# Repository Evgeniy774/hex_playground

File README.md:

# hex_playground
Simple STM32F411 based project for kids education purposes

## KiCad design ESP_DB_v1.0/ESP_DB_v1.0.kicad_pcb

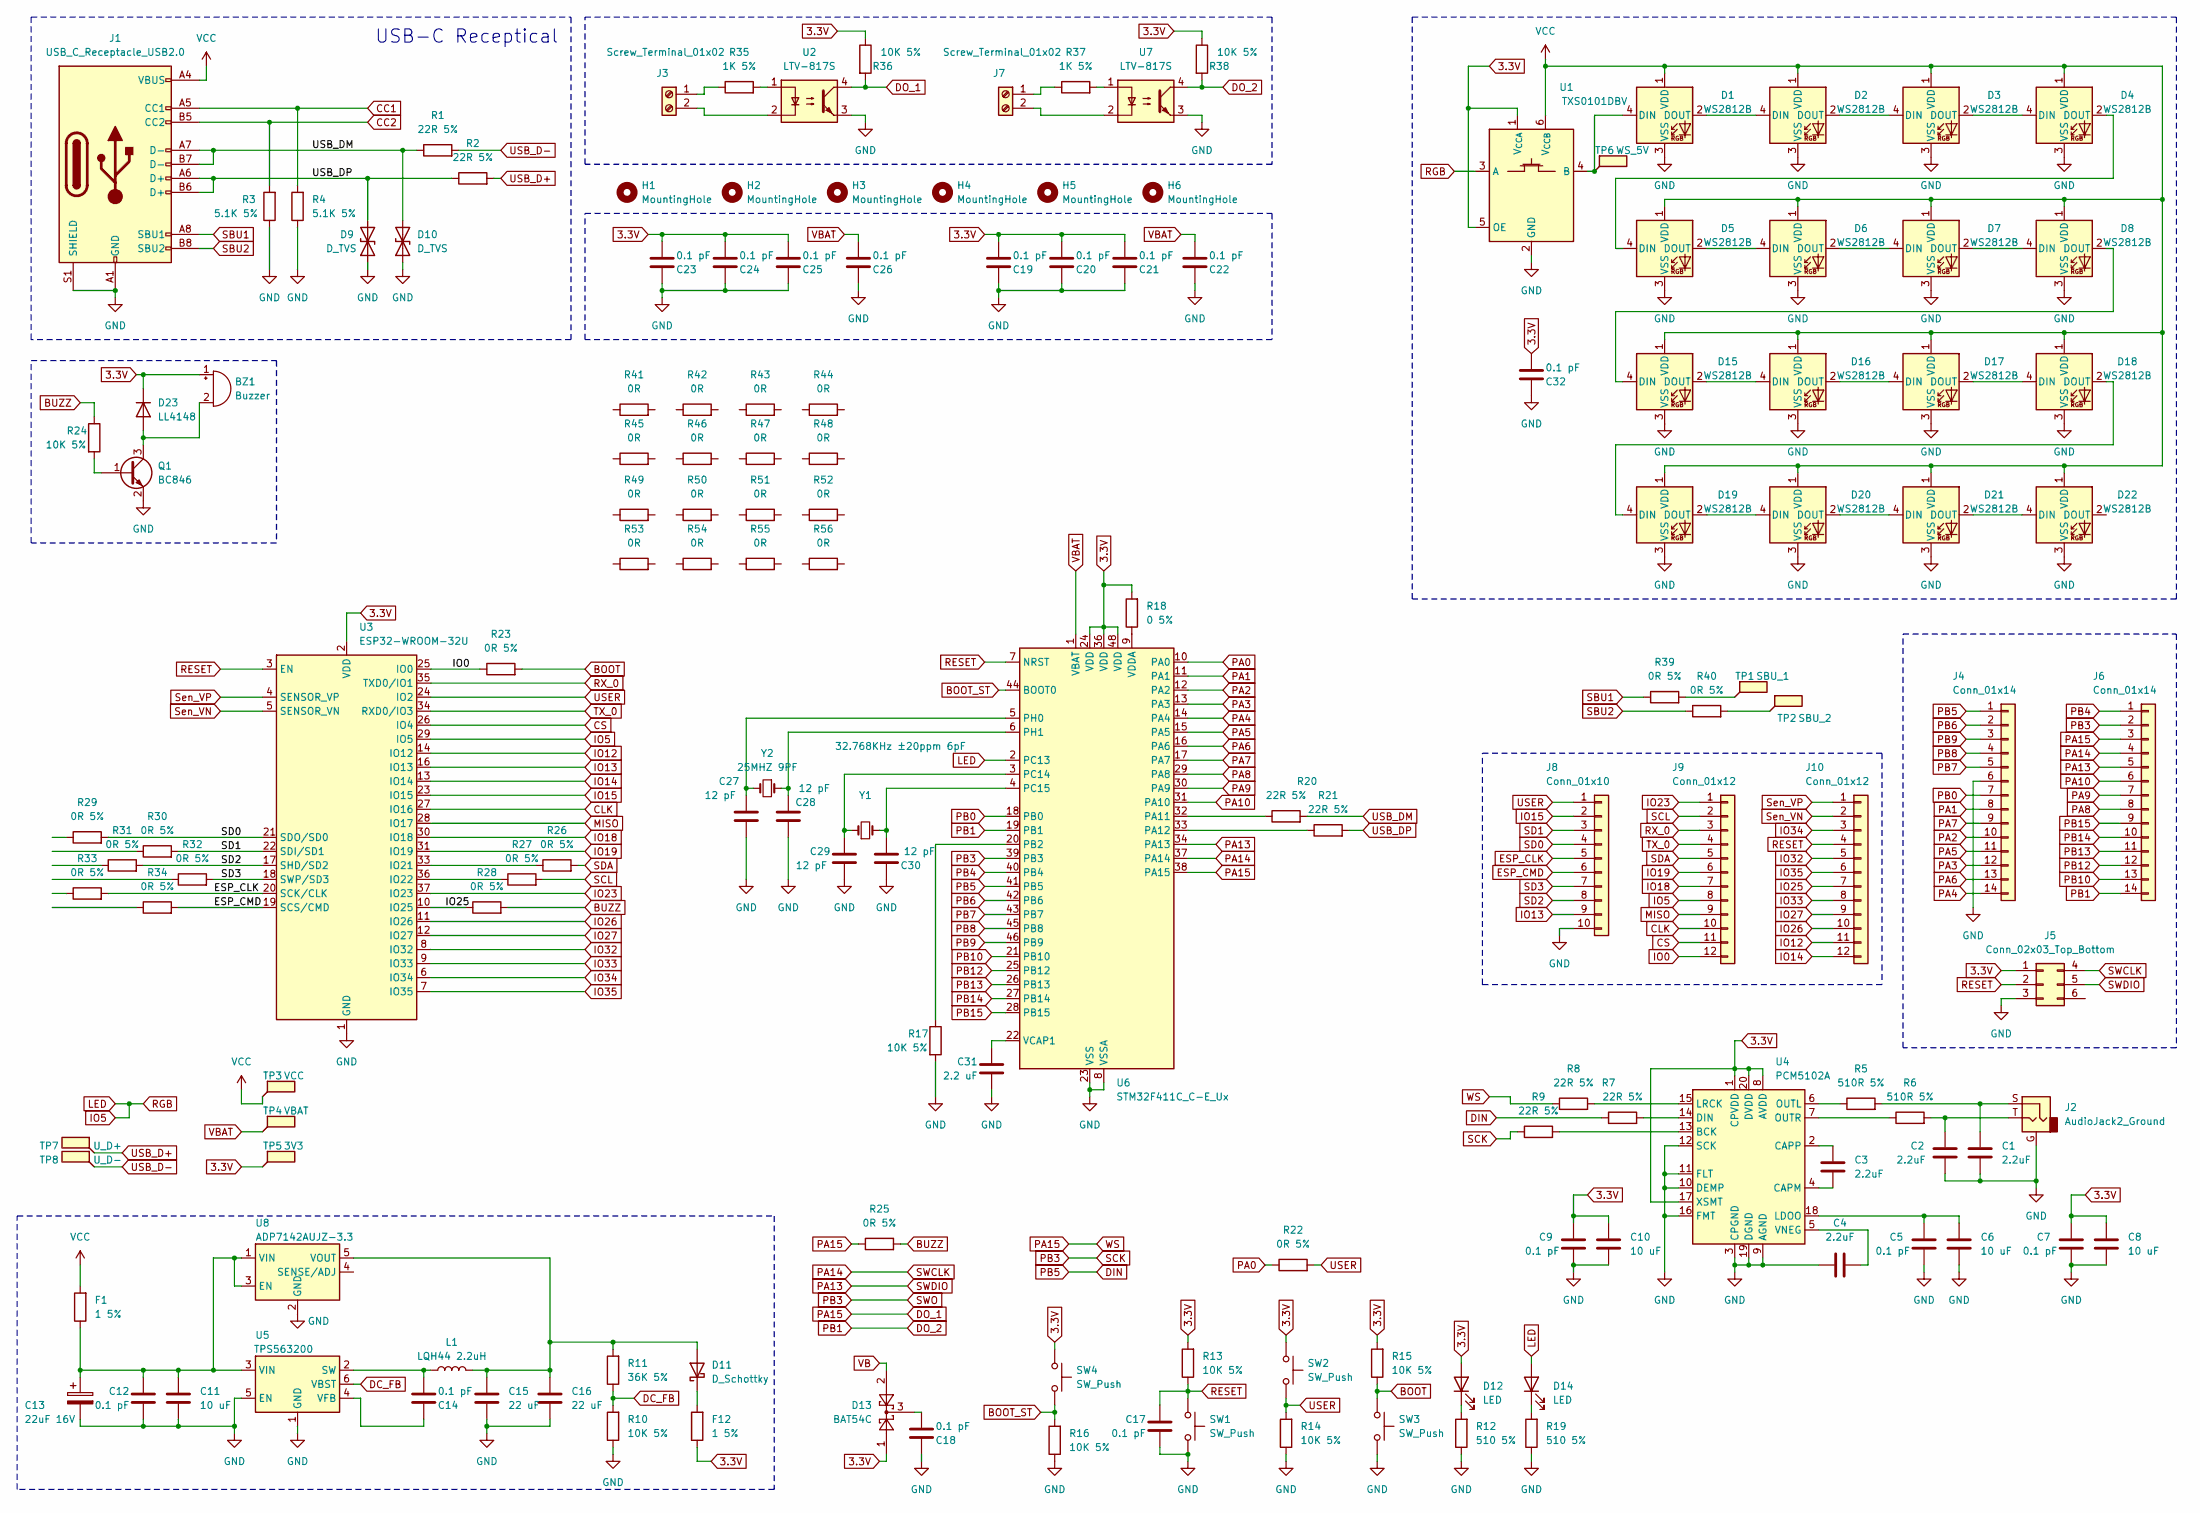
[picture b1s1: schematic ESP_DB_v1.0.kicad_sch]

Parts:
BZ1: Buzzer; Buzzer_D14mm_H7mm_P10mm
C1, C2, C3, C4: 2.2uF; C_0603_1608Metric_EK
C5, C7, C9, C12, C14, C17, C18, C19, C20, C21, C22, C23, C24, C25, C26, C32: 0.1 pF; C_0603_1608Metric_EK
C6, C8, C10, C11: 10 uF; C_0603_1608Metric_EK
C13: 22uF 16V; CP_EIA-3528-21_Kemet-B
C15, C16: 22 uF; C_0603_1608Metric_EK
C27, C28, C29, C30: 12 pF; C_0603_1608Metric_EK
C31: 2.2 uF; C_0603_1608Metric_EK
D1, D2, D3, D4, D5, D6, D7, D8, D15, D16, D17, D18, D19, D20, D21, D22: WS2812B; LED_WS2812B_PLCC4_5.0x5.0mm_P3.2mm
D9, D10: D_TVS; D_0805_2012Metric
D11: D_Schottky; D_SOD-123
D12, D14: LED; LED_0603_1608Metric
D13: BAT54C; SOT-23
D23: LL4148; D_MiniMELF
F1, F12: 1 5%; C_1206_3216Metric
H1, H2, H3, H4, H5, H6: MountingHole; MountingHole_3.2mm_M3_Pad_Via
J1: USB_C_Receptacle_USB2.0; USB_C_Receptacle_16_JAE_GT-USB-7010ASV
J2: AudioJack2_Ground; Jack_3.5mm_CUI_SJ1-3533NG_Horizontal
J3, J7: Screw_Terminal_01x02; PhoenixContact_MCV_1,5_2-G-3.81_1x02_P3.81mm_Vertical
J4, J6: Conn_01x14; PinHeader_2x07_P2.54mm_Vertical
J5: Conn_02x03_Top_Bottom; PinHeader_2x03_P2.00mm_Vertical
J8: Conn_01x10; PinHeader_1x10_P2.54mm_Vertical
J9, J10: Conn_01x12; PinHeader_2x06_P2.54mm_Vertical
L1: LQH44 2.2uH; L_Wurth_WE-LQSH-4020
Q1: BC846; SOT-23_EK
R1, R2, R7, R8, R9, R20, R21: 22R 5%; R_0603_1608Metric_EK
R3, R4: 5.1K 5%; R_0603_1608Metric_EK
R5, R6: 510R 5%; R_0603_1608Metric_EK
R10, R13, R14, R15, R16, R17, R24, R36, R38: 10K 5%; R_0603_1608Metric_EK
R11: 36K 5%; R_0603_1608Metric_EK
R12, R19: 510 5%; R_0603_1608Metric_EK
R18: 0 5%; R_0603_1608Metric_EK
R22, R23, R25, R26, R27, R28, R29, R30, R31, R32, R33, R34, R39, R40: 0R 5%; R_0603_1608Metric_EK
R35, R37: 1K 5%; R_0603_1608Metric_EK
R41, R42, R43, R44, R45, R46, R47, R48, R49, R50, R51, R52, R53, R54, R55, R56: 0R; R_0603_1608Metric_EK
SW1, SW2, SW3, SW4: SW_Push; SW_Push_1P1T_XKB_TS-1187A
TP1: SBU_1; TestPoint_Loop_D2.60mm_Drill0.9mm_Beaded
TP2: SBU_2; TestPoint_Loop_D2.60mm_Drill0.9mm_Beaded
TP3: VCC; TestPoint_Loop_D2.60mm_Drill0.9mm_Beaded
TP4: VBAT; TestPoint_Loop_D2.60mm_Drill0.9mm_Beaded
TP5: 3V3; TestPoint_Loop_D2.60mm_Drill0.9mm_Beaded
TP6: WS_5V; TestPoint_Loop_D2.60mm_Drill0.9mm_Beaded
TP7: U_D+; TestPoint_Keystone_5000-5004_Miniature
TP8: U_D-; TestPoint_Keystone_5000-5004_Miniature
U1: TXS0101DBV; SOT-23-6
U2, U7: LTV-817S; SMDIP-4_W9.53mm
U3: ESP32-WROOM-32U
U4: PCM5102A; TSSOP-20_4.4x6.5mm_P0.65mm
U5: TPS563200; SOT-23-6
U6: STM32F411C_C-E_Ux; QFN-48-1EP_7x7mm_P0.5mm_EP5.6x5.6mm
U8: ADP7142AUJZ-3.3; TSOT-23-5
Y1: 32.768KHz ±20ppm 6pF; Crystal_SMD_3215-2Pin_3.2x1.5mm
Y2: 25MHZ 9PF; Crystal_SMD_3225-4Pin_3.2x2.5mm

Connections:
3.3V: BZ1.1 (-), C7.1, C8.1, C9.1, C10.1, C19.2, C20.2, C21.2, C23.2, C24.2, C25.2, C32.2, D12.2 (A), D13.1, D23.1 (K), F12.1, J5.1, R13.2, R15.2, R18.2, R36.1, R38.1, SW2.1, SW4.1, TP5.1, U1.1 (V_{CCA}), U1.5 (OE), U3.2 (VDD), U4.1 (CPVDD), U4.8 (AVDD), U4.17 (XSMT), U4.20 (DVDD), U6.24 (VDD), U6.36 (VDD), U6.48 (VDD)
BOOT: R15.1, R23.2, SW3.1
BOOT_ST: R16.2, SW4.2, U6.44 (BOOT0)
BUZZ: R24.1, R25.2, R28.2
CC1: J1.A5 (CC1), R4.2
CC2: J1.B5 (CC2), R3.2
CLK: J9.10, U3.27 (IO16)
CS: J9.11, U3.26 (IO4)
DC_FB: R10.2, R11.1, U5.6 (VBST)
DIN: J4.1, R7.1, U6.41 (PB5)
DO_1: J6.3, R8.1, R25.1, R36.2, U2.4, U6.38 (PA15)
DO_2: J6.14, R38.2, U6.19 (PB1), U7.4
ESP_CLK: J8.5, R33.2, U3.20 (SCK/CLK)
ESP_CMD: J8.6, R34.2, U3.19 (SCS/CMD)
GND: C1.2, C2.2, C4.2, C5.2, C6.2, C7.2, C8.2, C9.2, C10.2, C11.2, C12.2, C13.2, C15.2, C16.2, C17.2, C18.1, C19.1, C20.1, C21.1, C22.1, C23.1, C24.1, C25.1, C26.1, C27.2, C28.1, C29.2, C30.1, C31.2, C32.1, D1.3 (VSS), D2.3 (VSS), D3.3 (VSS), D4.3 (VSS), D5.3 (VSS), D6.3 (VSS), D7.3 (VSS), D8.3 (VSS), D9.1 (A1), D10.1 (A1), D15.3 (VSS), D16.3 (VSS), D17.3 (VSS), D18.3 (VSS), D19.3 (VSS), D20.3 (VSS), D21.3 (VSS), D22.3 (VSS), J1.A1 (GND), J1.A12 (GND), J1.B1 (GND), J1.B12 (GND), J1.S1 (SHIELD), J2.G, J4.6, J5.3, J8.10, Q1.2 (E), R3.1, R4.1, R10.1, R12.1, R14.1, R16.1, R17.2, R19.1, SW1.2, SW3.2, U1.2 (GND), U2.3, U3.1 (GND), U3.15 (GND), U3.38 (GND), U3.39 (GND), U4.3 (CPGND), U4.9 (AGND), U4.10 (DEMP), U4.11 (FLT), U4.12 (SCK), U4.16 (FMT), U4.19 (DGND), U5.1 (GND), U5.5 (EN), U6.8 (VSSA), U6.23 (VSS), U6.35 (VSS), U6.47 (VSS), U6.49 (VSS), U7.3, U8.2 (GND)
IO0: J9.12, R23.1, U3.25 (IO0)
IO5: D14.2 (A), J9.8, U1.3 (A), U3.29 (IO5), U6.2 (PC13)
IO12: J10.11, U3.14 (IO12)
IO13: J8.9, U3.16 (IO13)
IO14: J10.12, U3.13 (IO14)
IO15: J8.2, U3.23 (IO15)
IO18: J9.7, U3.30 (IO18)
IO19: J9.6, U3.31 (IO19)
IO23: J9.1, U3.37 (IO23)
IO25: J10.7, R28.1, U3.10 (IO25)
IO26: J10.10, U3.11 (IO26)
IO27: J10.9, U3.12 (IO27)
IO32: J10.5, U3.8 (IO32)
IO33: J10.8, U3.9 (IO33)
IO34: J10.3, U3.6 (IO34)
IO35: J10.6, U3.7 (IO35)
MISO: J9.9, U3.28 (IO17)
unnamed: BZ1.2 (+), D23.2 (A), Q1.3 (C)
unnamed: C1.1, J2.S, R5.2
unnamed: C2.1, J2.T, R6.2
unnamed: C18.2, D13.3
unnamed: D1.4 (DIN), TP6.1, U1.4 (B)
unnamed: D1.2 (DOUT), D2.4 (DIN)
unnamed: D2.2 (DOUT), D3.4 (DIN)
unnamed: D3.2 (DOUT), D4.4 (DIN)
unnamed: D4.2 (DOUT), D5.4 (DIN)
unnamed: D5.2 (DOUT), D6.4 (DIN)
unnamed: D6.2 (DOUT), D7.4 (DIN)
unnamed: D7.2 (DOUT), D8.4 (DIN)
unnamed: C15.1, C16.1, D11.2 (A), L1.2, R11.2, U8.5 (VOUT)
unnamed: D11.1 (K), F12.2
unnamed: D12.1 (K), R12.2
unnamed: D14.1 (K), R19.2
unnamed: D8.2 (DOUT), D15.4 (DIN)
unnamed: D15.2 (DOUT), D16.4 (DIN)
unnamed: D16.2 (DOUT), D17.4 (DIN)
unnamed: D17.2 (DOUT), D18.4 (DIN)
unnamed: D18.2 (DOUT), D19.4 (DIN)
unnamed: D19.2 (DOUT), D20.4 (DIN)
unnamed: D20.2 (DOUT), D21.4 (DIN)
unnamed: D21.2 (DOUT), D22.4 (DIN)
unnamed: J3.1, R35.1
unnamed: J3.2, U2.2
unnamed: J7.1, R37.1
unnamed: J7.2, U7.2
unnamed: Q1.1 (B), R24.2
unnamed: R35.2, U2.1
unnamed: R37.2, U7.1
unnamed: R39.2, TP1.1
unnamed: R40.2, TP2.1
unnamed: R26.1, U3.33 (IO21)
unnamed: R27.1, U3.36 (IO22)
unnamed: R9.2, U4.13 (BCK)
unnamed: C3.2, U4.4 (CAPM)
unnamed: C3.1, U4.2 (CAPP)
unnamed: R7.2, U4.14 (DIN)
unnamed: C5.1, C6.1, U4.18 (LDOO)
unnamed: R8.2, U4.15 (LRCK)
unnamed: R5.1, U4.6 (OUTL)
unnamed: R6.1, U4.7 (OUTR)
unnamed: C4.1, U4.5 (VNEG)
unnamed: C14.2, L1.1, U5.2 (SW)
unnamed: C14.1, U5.4 (VFB)
unnamed: C11.1, C12.1, C13.1, F1.1, U5.3 (VIN), U8.1 (VIN), U8.3 (EN)
unnamed: R20.1, U6.32 (PA11)
unnamed: R21.1, U6.33 (PA12)
unnamed: R17.1, U6.20 (PB2)
unnamed: C29.1, U6.3 (PC14), Y1.1
unnamed: C30.2, U6.4 (PC15), Y1.2
unnamed: C27.1, U6.5 (PH0), Y2.2
unnamed: C28.2, U6.6 (PH1), Y2.1
unnamed: C31.1, U6.22 (VCAP1)
unnamed: R18.1, U6.9 (VDDA)
PA0: R22.1, U6.10 (PA0)
PA1: J4.8, U6.11 (PA1)
PA2: J4.10, U6.12 (PA2)
PA3: J4.12, U6.13 (PA3)
PA4: J4.14, U6.14 (PA4)
PA5: J4.11, U6.15 (PA5)
PA6: J4.13, U6.16 (PA6)
PA7: J4.9, U6.17 (PA7)
PA8: J6.8, U6.29 (PA8)
PA9: J6.7, U6.30 (PA9)
PA10: J6.6, U6.31 (PA10)
PA13: J5.5, J6.5, U6.34 (PA13)
PA14: J5.4, J6.4, U6.37 (PA14)
PB0: J4.7, U6.18 (PB0)
PB3: J6.2, R9.1, U6.39 (PB3)
PB4: J6.1, U6.40 (PB4)
PB6: J4.2, U6.42 (PB6)
PB7: J4.5, U6.43 (PB7)
PB8: J4.4, U6.45 (PB8)
PB9: J4.3, U6.46 (PB9)
PB10: J6.13, U6.21 (PB10)
PB12: J6.12, U6.25 (PB12)
PB13: J6.11, U6.26 (PB13)
PB14: J6.10, U6.27 (PB14)
PB15: J6.9, U6.28 (PB15)
RESET: C17.1, J5.2, J10.4, R13.1, SW1.1, U3.3 (EN), U6.7 (NRST)
RX_0: J9.3, U3.35 (TXD0/IO1)
SBU1: J1.A8 (SBU1), R39.1
SBU2: J1.B8 (SBU2), R40.1
SCL: J9.2, R27.2
SD0: J8.4, R29.2, U3.21 (SDO/SD0)
SD1: J8.3, R30.2, U3.22 (SDI/SD1)
SD2: J8.8, R31.2, U3.17 (SHD/SD2)
SD3: J8.7, R32.2, U3.18 (SWP/SD3)
SDA: J9.5, R26.2
Sen_VN: J10.2, U3.5 (SENSOR_VN)
Sen_VP: J10.1, U3.4 (SENSOR_VP)
TX_0: J9.4, U3.34 (RXD0/IO3)
USB_D+: R2.2, TP7.1
USB_D-: R1.2, TP8.1
USB_DM: D10.2 (A2), J1.A7 (D-), J1.B7 (D-), R1.1, R20.2
USB_DP: D9.2 (A2), J1.A6 (D+), J1.B6 (D+), R2.1, R21.2
USER: J8.1, R14.2, R22.2, SW2.2, U3.24 (IO2)
VB: D13.2
VBAT: C22.2, C26.2, TP4.1, U6.1 (VBAT)
VCC: D1.1 (VDD), D2.1 (VDD), D3.1 (VDD), D4.1 (VDD), D5.1 (VDD), D6.1 (VDD), D7.1 (VDD), D8.1 (VDD), D15.1 (VDD), D16.1 (VDD), D17.1 (VDD), D18.1 (VDD), D19.1 (VDD), D20.1 (VDD), D21.1 (VDD), D22.1 (VDD), F1.2, J1.A4 (VBUS), J1.A9 (VBUS), J1.B4 (VBUS), J1.B9 (VBUS), TP3.1, U1.6 (V_{CCB})

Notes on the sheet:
USB-C Receptical

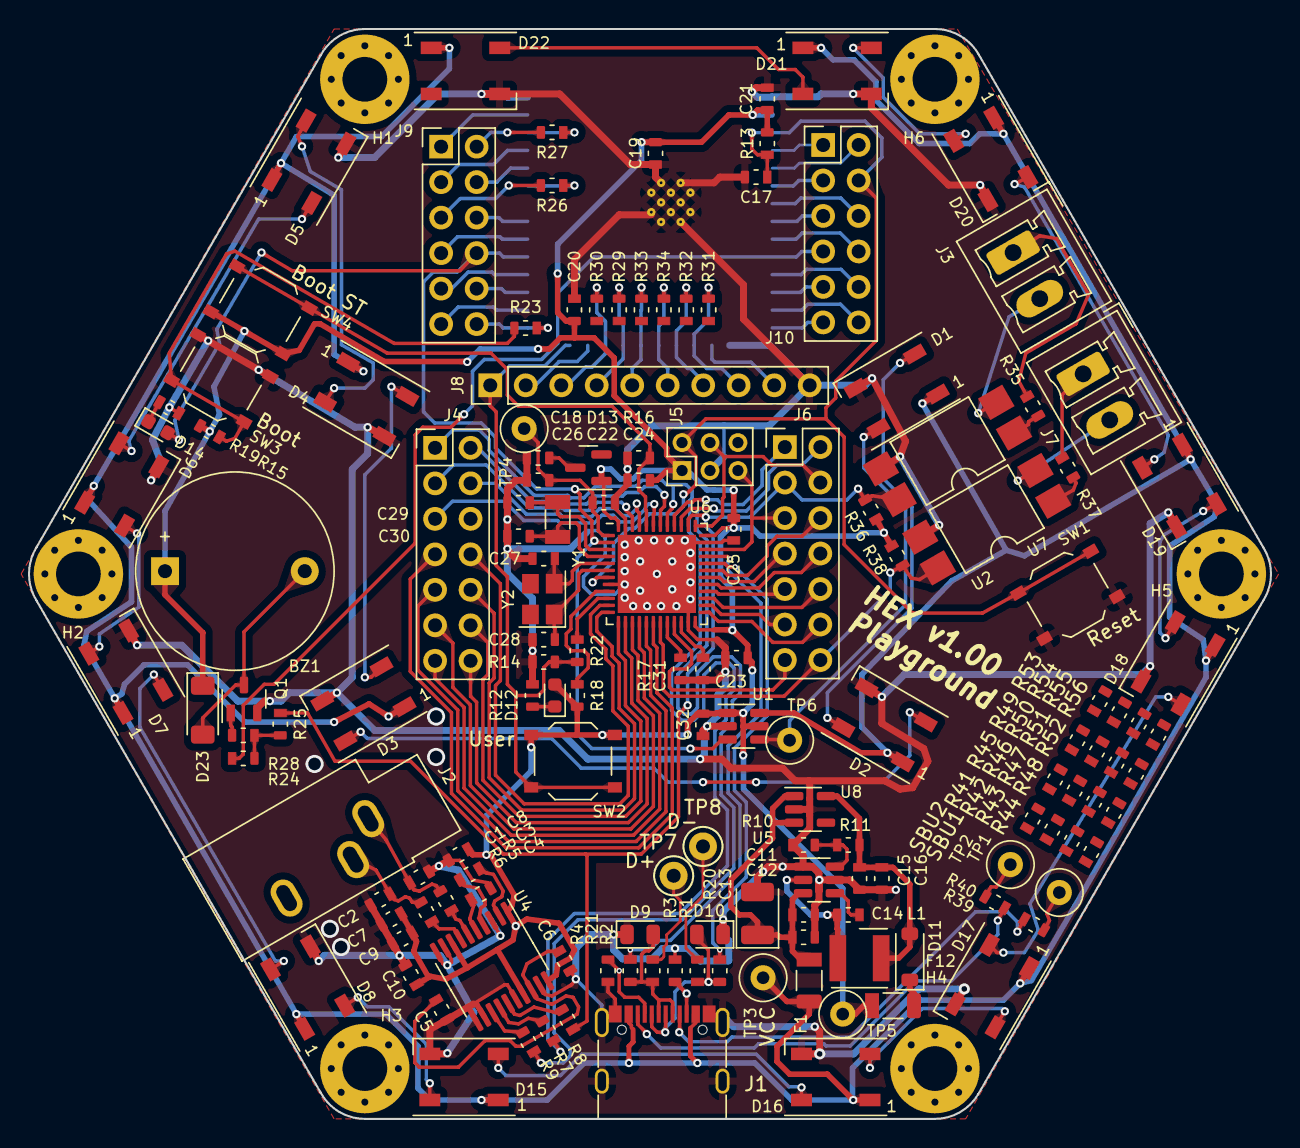
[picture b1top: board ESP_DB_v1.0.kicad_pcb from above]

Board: 2 copper layers, 88.9 x 78.0 mm, 154 parts (1 on the bottom side), 133 nets.

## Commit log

2024-05-29 First version of PCB
